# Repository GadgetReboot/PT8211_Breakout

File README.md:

# PT8211_Breakout
<br><br><BR><BR>
Breakout board with headers for the PT8211 I2S DAC

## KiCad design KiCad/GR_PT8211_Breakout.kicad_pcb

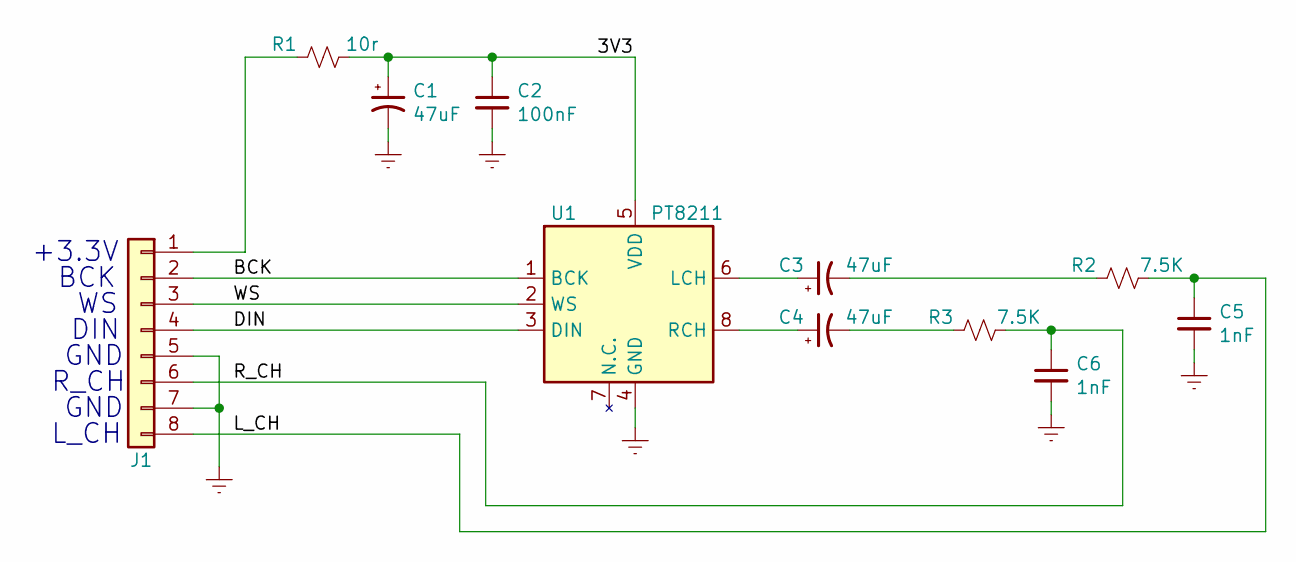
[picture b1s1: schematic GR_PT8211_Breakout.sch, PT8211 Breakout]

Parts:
C1, C3, C4: 47uF; C_Elec_4x5.4
C2: 100nF; C_0805_2012Metric_Pad1.15x1.40mm_HandSolder
C5, C6: 1nF; C_0805_2012Metric_Pad1.15x1.40mm_HandSolder
J1: Conn_01x08; PinHeader_1x08_P2.54mm_Vertical
R1: 10r; R_0805_2012Metric_Pad1.15x1.40mm_HandSolder
R2, R3: 7.5K; R_0805_2012Metric_Pad1.15x1.40mm_HandSolder
U1: PT8211; SOIC-8_3.9x4.9mm_P1.27mm

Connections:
/3V3: C1.1, C2.1, R1.1, U1.5 (VDD)
/BCK: J1.2, U1.1 (BCK)
/DIN: J1.4, U1.3 (DIN)
/L_CH: C5.1, J1.8, R2.1
/R_CH: C6.1, J1.6, R3.1
/WS: J1.3, U1.2 (WS)
GNDREF: C1.2, C2.2, C5.2, C6.2, J1.5, J1.7, U1.4 (GND)
unnamed: C3.1, U1.6 (LCH)
unnamed: C3.2, R2.2
unnamed: C4.1, U1.8 (RCH)
unnamed: C4.2, R3.2
unnamed: J1.1, R1.2

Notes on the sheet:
L_CH
R_CH
+3.3V
BCK
DIN
GND

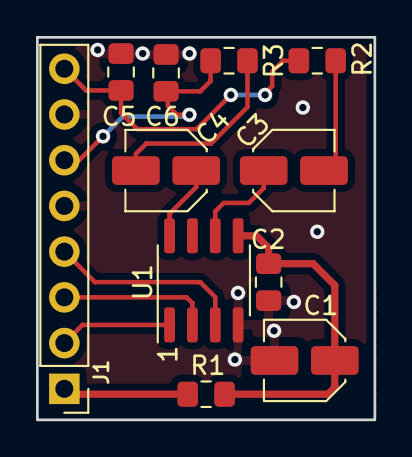
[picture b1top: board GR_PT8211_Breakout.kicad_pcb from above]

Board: 2 copper layers, 18.8 x 21.2 mm, 11 parts (0 on the bottom side), 12 nets.
